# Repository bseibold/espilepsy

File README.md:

ESPilepsy
=========

A small ESP32 board to drive 2 LED strips, intended to be used with [WLED](https://kno.wled.ge/)

## Status

Assembled, initial testing done

## Features and non-features

 - Only 5V LED strips
 - Works with at least 6A current
 - LEDs can be powered down via FET (no relay)
 - Normal fuse, no poly-fuse
 - No IR receiver
 - No reverse voltage protection
 - No built-in USB-to-UART

## Design constraints

 - Design rules compatible with [JLCPCB](https://jlcpcb.com/) (because it's cheap)
 - Use only parts available at [Reichelt](https://www.reichelt.de/) (because it's convenient)
 - If possible, use widely-used parts
 - SMD parts no smaller than 0603
 - pin spacing at least about 1mm (SOT23-5 is about the smallest acceptable)

## Bill of materials

(Work in progress)

### ESP32

All ESP32-WROOM-32x modules seem to be pin-compatible.

Reichelt:
 - [ESP32-WROOM-32D](https://www.reichelt.de/wifi-smd-modul-esp32-d0wd-4-mb-spi-3-3-v-18-x-25-5-x-3-2-mm-esp32wroom32d-p300012.html)
 - [ESP32-WROOM-32E-N4](https://www.reichelt.de/wifi-smd-modul-esp32-d0wd-v3-16-mb-spi-3-3-v-18-x-25-5-x-3-1-esp32wroom32e16-p300025.html)
 - [ESP32-WROOM-32E-N8](https://www.reichelt.de/wifi-modul-802-11-bt-2-4-2-5ghz-150mb-s-esp32wroom32e8-p311740.html)
 - [ESP32-WROOM-32E-N16](https://www.reichelt.de/wifi-smd-modul-esp32-d0wd-v3-16-mb-spi-3-3-v-18-x-25-5-x-3-1-esp32wroom32e16-p300025.html)

### High-side switch

There are lots of parts that can be used here

 - must be enhancement-type p-FET
 - SO-8 package
 - Vg(th) should be low enough that the FET is full on at ~4.5V
 
Reichelt: 
 - [AO4407A](https://www.reichelt.de/mosfet-p-kanal-30-v-12-a-rds-on-0-0085-ohm-so-8-ao-4407a-p166495.html)
 - [IRF9310](https://www.reichelt.de/mosfet-p-ch-30v-20a-2-5w-so-8-irf-9310-p132127.html)
 - [TSM160P02CS](https://www.reichelt.de/mosfet-p-ch-20v-11a-0-016r-so8-tsm160p02cs-p254930.html)

### Level Shifter

One-gate versions of the 74xx125 will fit, but will require the pull-down resistor on pin 1 to be mounted. The selected variant must be compatible with LVCMOS input voltages, so 74HCT, 74AHCT, 74VHCT, etc.

Reichelt:
 - [M74VHC1GT50](https://www.reichelt.de/buffer-cmos-1-65--5-5-v-sot-23-5-m74vhc1gt50dtt1g-p219278.html)

### Enclosure

Reichelt:
 - [4U32100603006](https://www.reichelt.de/industriegehaeuse-76-x-59-x-28-mm-ip54-schwarz-4u32100603006-p324273.html)

### Screw Terminals

AKL073 from Reichelt won't fit into the enclosure.

Reichelt:
 - [AKL 101-02](https://www.reichelt.de/anschlussklemme-2-pol-2-mm-rm-5-08-akl-101-02-p36605.html)
 - [CTB0509-2](https://www.reichelt.de/loetbare-schraubklemme-2-pol-rm-5-08-mm-90--ctb0509-2-p292701.html)

## Similar projects

If this doesn't fit your needs, check out these other cool boards:

 - [Yet Another WLED Controller](https://github.com/lizardsystems/yawl-controller)

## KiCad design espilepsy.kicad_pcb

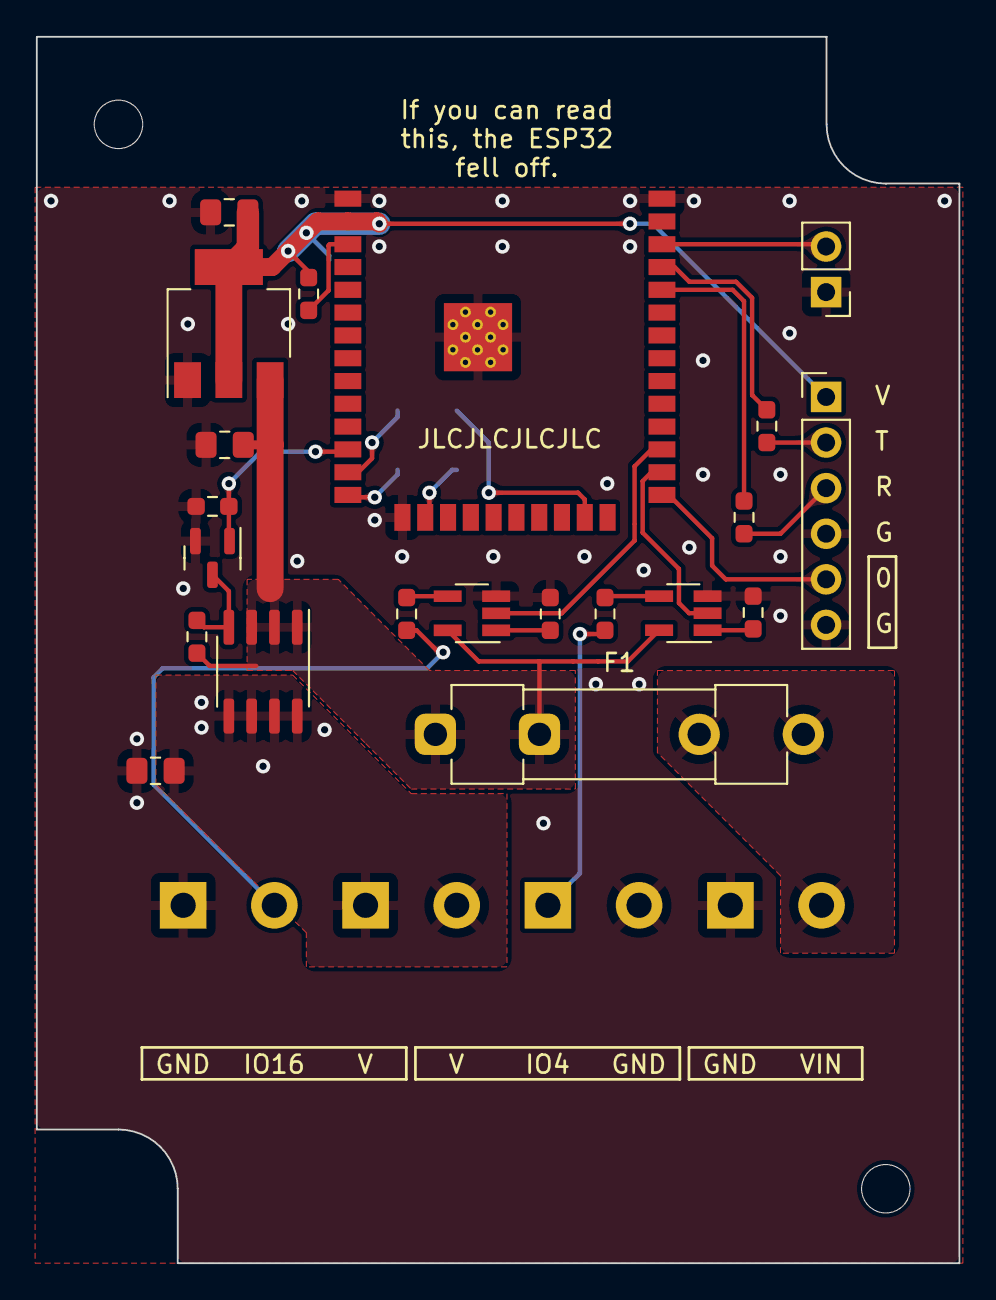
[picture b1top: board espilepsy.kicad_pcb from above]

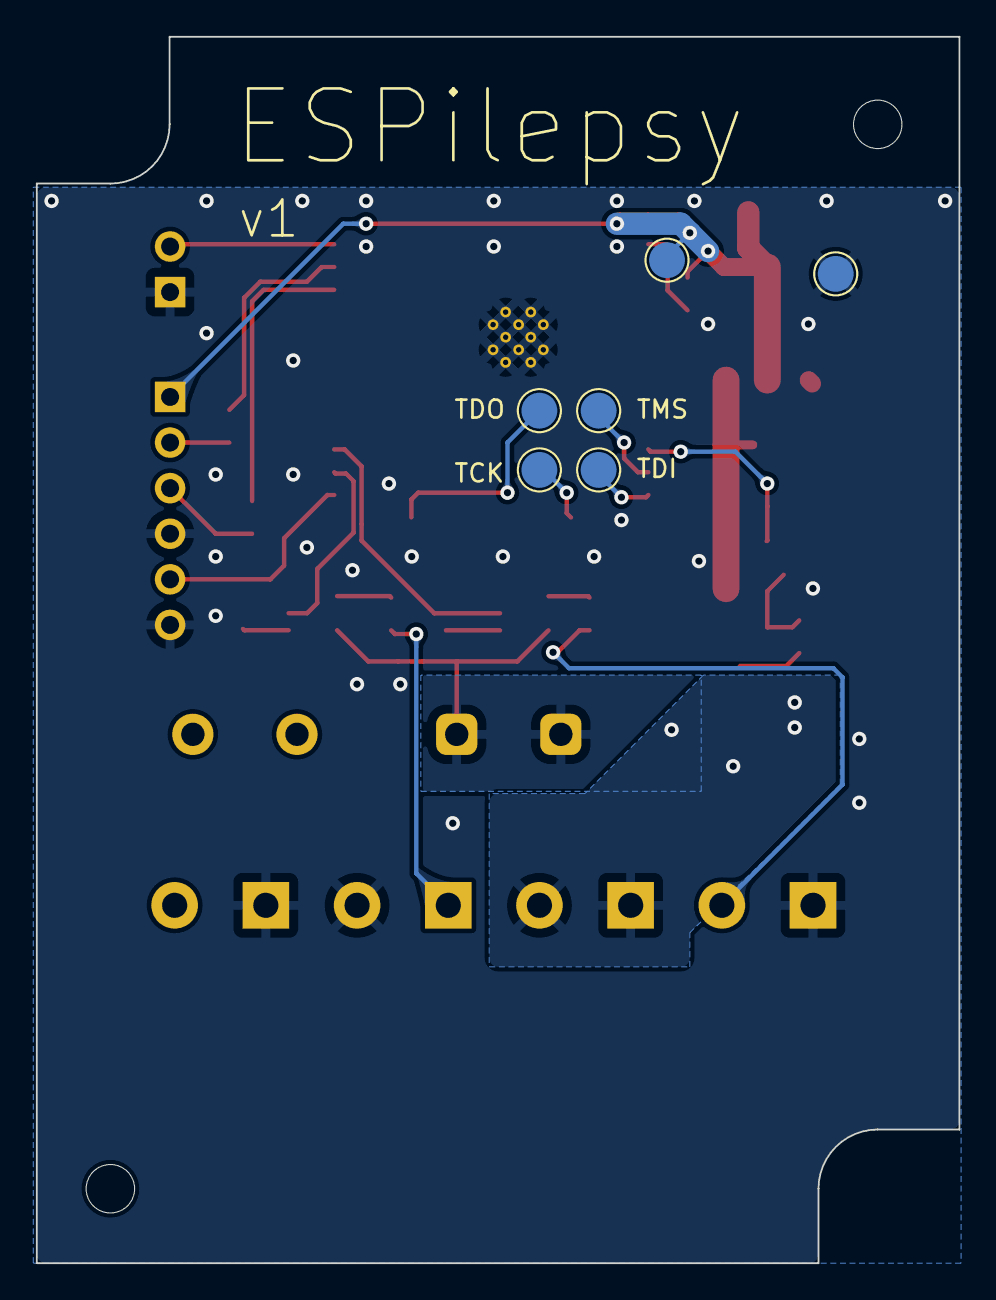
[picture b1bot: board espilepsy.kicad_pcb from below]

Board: 2 copper layers, 51.4 x 68.3 mm, 33 parts (6 on the bottom side), 26 nets.

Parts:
C1, C2, C3: 10u; C_0805_2012Metric_Pad1.18x1.45mm_HandSolder
F1: Fuse_Small; Fuseholder_Clip-5x20mm_Littelfuse_520_Inline_P20.50x5.80mm_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
H1, H2: MountingHole; MountingHole_2.7mm_M2.5
J1: Conn_01x06; PinHeader_1x06_P2.54mm_Vertical
J2, J3, J4, J5: Screw_Terminal_01x02; TerminalBlock_MetzConnect_Type073_RT02602HBLU_1x02_P5.08mm_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
J6: Conn_01x02_Pin; PinHeader_1x02_P2.54mm_Vertical
Q1: BSS138; SOT-23
Q2: IRF9310; SOIC-8_3.9x4.9mm_P1.27mm
R1, R4, R5, R8, R9: 10k; R_0603_1608Metric_Pad0.98x0.95mm_HandSolder
R6, R7, R10, R11: 100; R_0603_1608Metric_Pad0.98x0.95mm_HandSolder
TP1, TP2, TP3, TP4, TP5, TP6: TestPoint; TestPoint_Pad_D2.0mm
U1: NCP1117-3.3_SOT223; SOT-223-3_TabPin2
U2, U4: M74VHC1GT50; SOT-23-5_HandSoldering
U3: ESP32-WROOM-32D; ESP32-WROOM-32D-JLCPCB

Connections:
+3.3V: C1.1, J1.1, R1.2, TP1.1, U1.2 (VO), U3.2 (VDD)
+5V: C2.1, F1.1, Q2.1 (S), Q2.2 (S), Q2.3 (S), R5.1, U1.3 (VI), U2.5 (VCC), U4.5 (VCC)
/BTN_1: J6.2, U3.36 (IO22)
/EN: R1.1, U3.3 (EN)
/IO0: J1.5, U3.25 (IO0)
/LED_5V: C3.1, J3.1, J3.2, Q2.5 (D), Q2.6 (D), Q2.7 (D), Q2.8 (D)
/LED_DATA_0: U3.27 (IO16), U4.2
/LED_DATA_0_OUT: J2.2, R7.2
/LED_DATA_1: U2.2, U3.26 (IO4)
/LED_DATA_1_OUT: J4.1, R6.2
/LED_POWER: Q1.1 (G), R4.1, U3.12 (IO27)
/TCK: TP4.1, U3.16 (IO13)
/TDI: TP3.1, U3.14 (IO12)
/TDO: TP5.1, U3.23 (IO15)
/TMS: TP2.1, U3.13 (IO14)
/UART_RX: J1.3, R10.2
/UART_TX: J1.2, R11.2
/VIN: F1.2, J5.2
GND: C1.2, C2.2, C3.2, J1.4, J1.6, J2.1, J4.2, J5.1, J6.1, Q1.2 (S), R4.2, R8.2, R9.2, TP6.1, U1.1 (ADJ), U2.3 (GND), U3.1 (GND), U3.15 (GND), U3.38 (GND), U3.39 (GND), U4.3 (GND)
unnamed: Q1.3 (D), Q2.4 (G), R5.2
unnamed: R6.1, U2.4
unnamed: R7.1, U4.4
unnamed: R8.1, U4.1
unnamed: R9.1, U2.1
unnamed: R10.1, U3.34 (RXD0/IO3)
unnamed: R11.1, U3.35 (TXD0/IO1)

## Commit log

2023-04-20 First draft
2023-05-04 Build v1
2023-05-18 Status Update
